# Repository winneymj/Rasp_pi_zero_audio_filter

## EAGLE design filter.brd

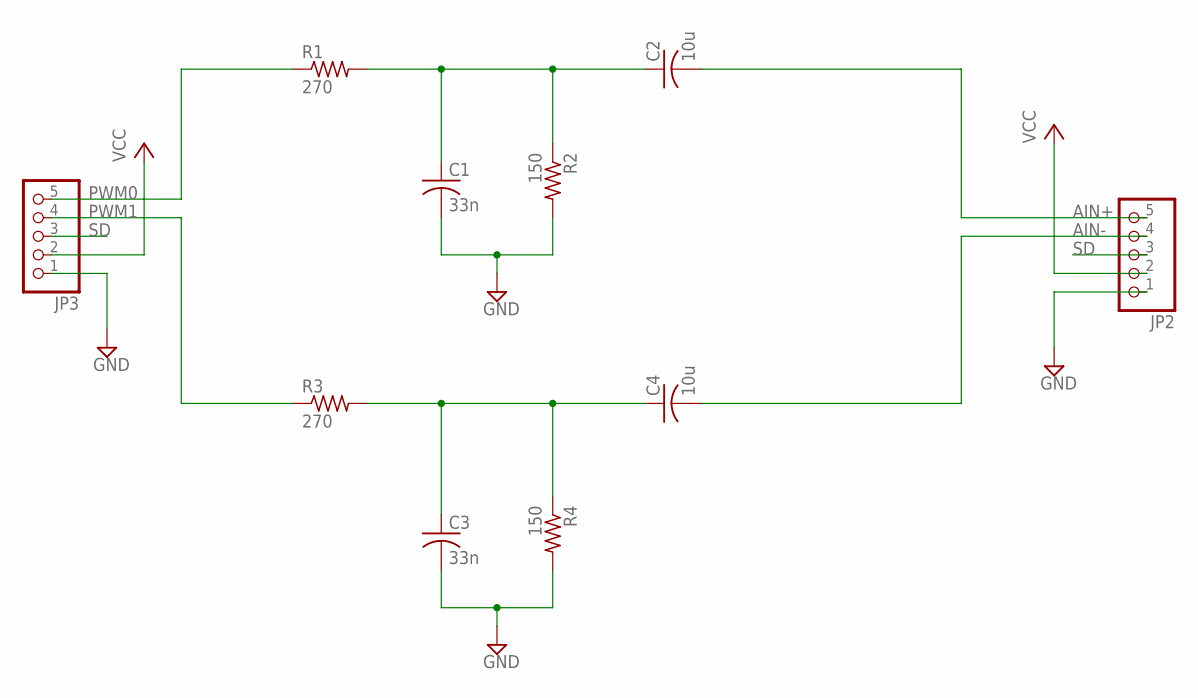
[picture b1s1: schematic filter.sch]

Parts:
C1, C3: 33n; C0805
C2, C4: 10u; C0805
JP2, JP3: PINHD-1X5; 1X05
R1, R3: 270; M0805
R2, R4: 150; M0805

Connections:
AIN+: C2.2, JP2.5
AIN-: C4.2, JP2.4
GND: C1.2, C3.2, JP2.1, JP3.1, R2.2, R4.2
unnamed: C1.1, C2.1, R1.2, R2.1
unnamed: C3.1, C4.1, R3.2, R4.1
PWM0: JP3.5, R1.1
PWM1: JP3.4, R3.1
SD: JP2.3, JP3.3
VCC: JP2.2, JP3.2

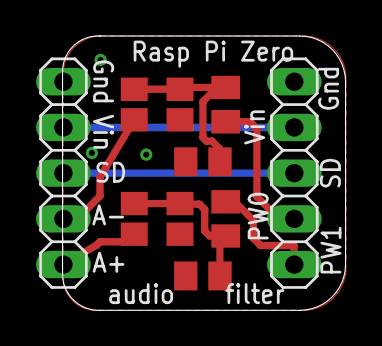
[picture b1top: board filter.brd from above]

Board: 2 copper layers, 15.7 x 15.2 mm, 10 parts (0 on the bottom side), 9 nets.

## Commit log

2016-10-10 Initial Version
